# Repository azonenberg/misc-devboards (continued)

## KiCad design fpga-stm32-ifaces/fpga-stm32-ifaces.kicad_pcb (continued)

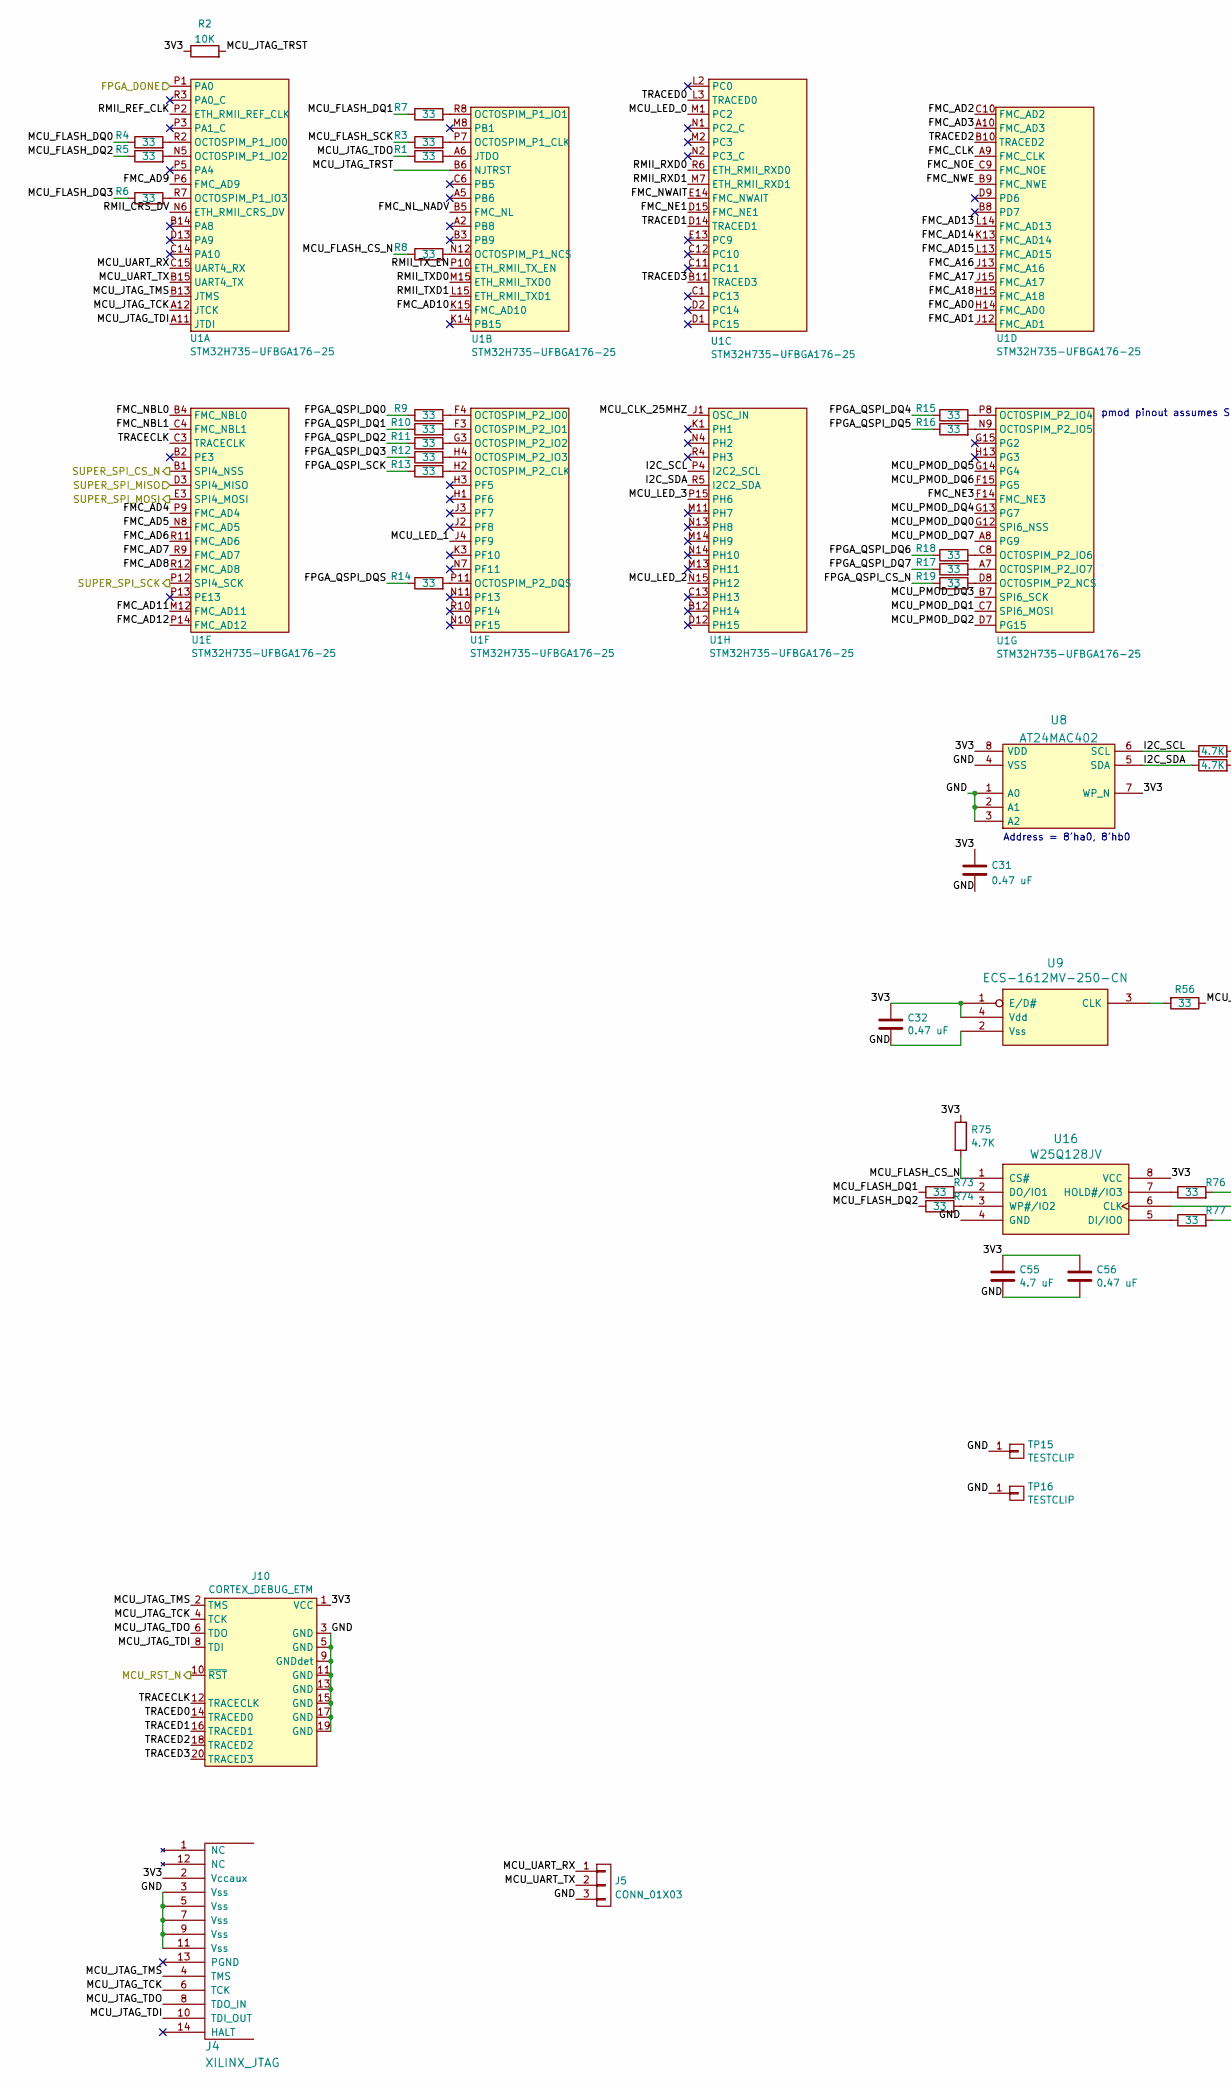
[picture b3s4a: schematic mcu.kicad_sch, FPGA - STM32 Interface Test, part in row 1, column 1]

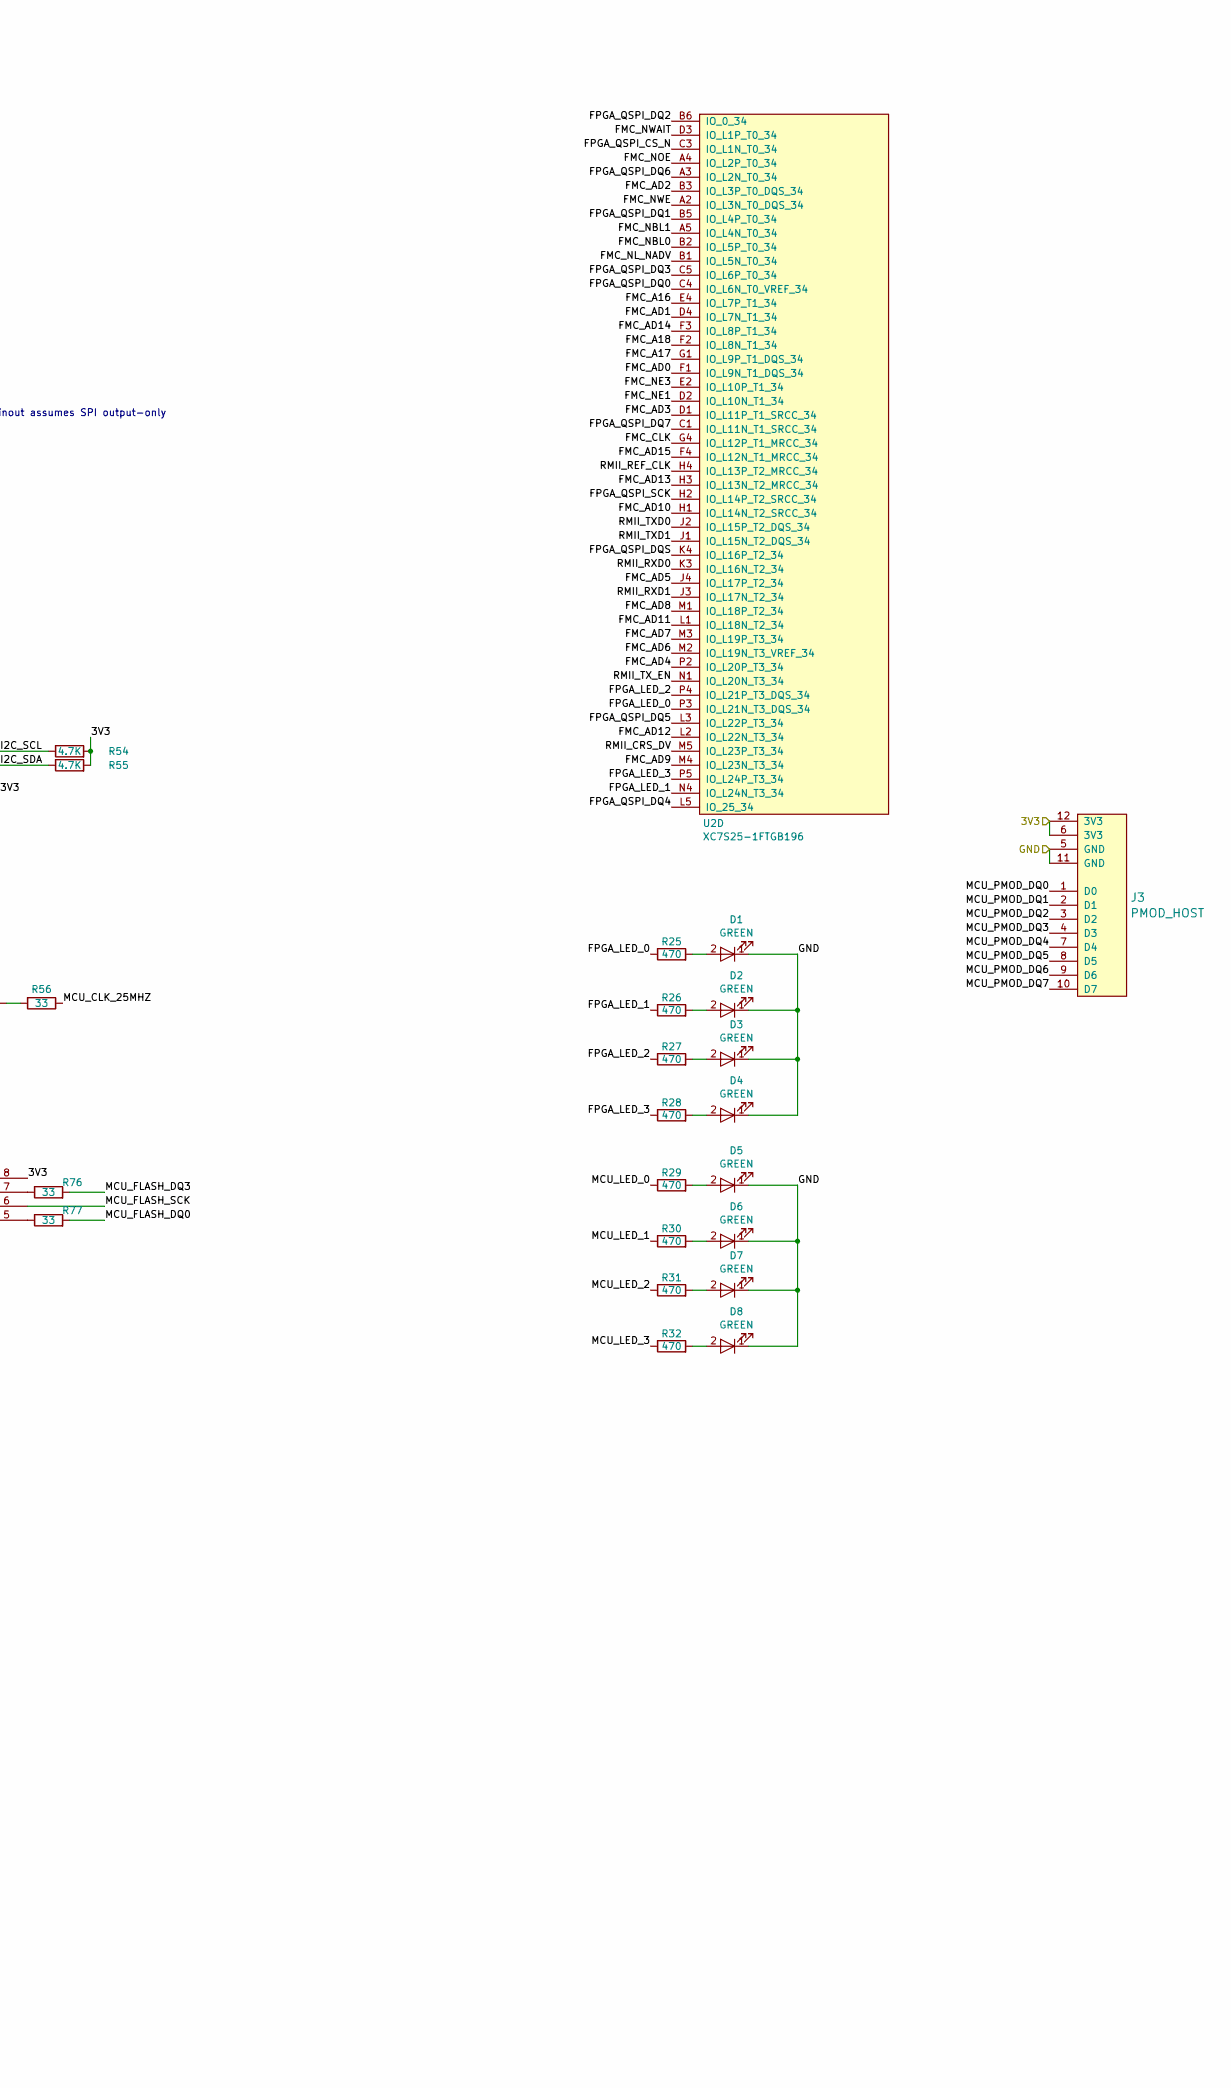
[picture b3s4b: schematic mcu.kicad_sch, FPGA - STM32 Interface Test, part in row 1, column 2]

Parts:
C31, C32, C56: 0.47 uF; EIA_0402_CAP_NOSILK
C55: 4.7 uF; EIA_0603_CAP_NOSILK
D1, D2, D3, D4, D5, D6, D7, D8: GREEN; EIA_0603_LED
J3: PMOD_HOST; CONN_HEADER_2.54MM_2x6_RA_PMOD_HOST
J4: XILINX_JTAG; XILINX_JTAG_PTH_MOLEX_0878311420
J5: CONN_01X03; CONN_HEADER_2.54MM_1x3
J10: CORTEX_DEBUG_ETM; CONN_HEADER_1.27MM_2x10_SMT_SAMTEC_FTSH-110-01-L-DV-K
R1, R3, R4, R5, R6, R7, R8, R9, R10, R11, R12, R13, R14, R15, R16, R17, R18, R19, R56, R73, R74, R76, R77: 33; EIA_0402_RES_NOSILK
R2: 10K; EIA_0402_RES_NOSILK
R25, R26, R27, R28, R29, R30, R31, R32: 470; EIA_0402_RES_NOSILK
R54, R55, R75: 4.7K; EIA_0402_RES_NOSILK
TP15, TP16: TESTCLIP; TESTPOINT_SMT_KEYSTONE_5016
U1: STM32H735-UFBGA176-25; BGA_201_10x10_DEPOP_0.65MM_OSHPARK
U2: XC7S25-1FTGB196; BGA_196_15x15_FULLARRAY_1MM_FTGB196
U8: AT24MAC402; DFN_8_0.5MM_2x3MM_TALL
U9: ECS-1612MV-250-CN; OSCILLATOR_1.6x1.2
U16: W25Q128JV; DFN_8_1.27MM_6x5MM

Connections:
/3V3: C31.1, C32.1, C55.1, C56.1, J3.6 (3V3), J3.12 (3V3), J4.2 (Vccaux), J10.1 (VCC), R2.1, R54.2, R55.2, R75.1, U8.7 (WP_N), U8.8 (VDD), U9.1 (E/D#), U9.4 (Vdd), U16.8 (VCC); also elsewhere on the board
/FPGA_DONE: U1.P1 (PA0); also elsewhere on the board
/GND: C31.2, C32.2, C55.2, C56.2, D1.1 (K), D2.1 (K), D3.1 (K), D4.1 (K), D5.1 (K), D6.1 (K), D7.1 (K), D8.1 (K), J3.5 (GND), J3.11 (GND), J4.3 (Vss), J4.5 (Vss), J4.7 (Vss), J4.9 (Vss), J4.11 (Vss), J5.3, J10.3 (GND), J10.5 (GND), J10.9 (GNDdet), J10.11 (GND), J10.13 (GND), J10.15 (GND), J10.17 (GND), J10.19 (GND), TP15.1, TP16.1, U8.1 (A0), U8.2 (A1), U8.3 (A2), U8.4 (VSS), U9.2 (Vss), U16.4 (GND); also elsewhere on the board
/MCU/FMC_A16: U1.J13 (FMC_A16), U2.E4 (IO_L7P_T1_34)
/MCU/FMC_A17: U1.J15 (FMC_A17), U2.G1 (IO_L9P_T1_DQS_34)
/MCU/FMC_A18: U1.H15 (FMC_A18), U2.F2 (IO_L8N_T1_34)
/MCU/FMC_AD0: U1.H14 (FMC_AD0), U2.F1 (IO_L9N_T1_DQS_34)
/MCU/FMC_AD1: U1.J12 (FMC_AD1), U2.D4 (IO_L7N_T1_34)
/MCU/FMC_AD2: U1.C10 (FMC_AD2), U2.B3 (IO_L3P_T0_DQS_34)
/MCU/FMC_AD3: U1.A10 (FMC_AD3), U2.D1 (IO_L11P_T1_SRCC_34)
/MCU/FMC_AD4: U1.P9 (FMC_AD4), U2.P2 (IO_L20P_T3_34)
/MCU/FMC_AD5: U1.N8 (FMC_AD5), U2.J4 (IO_L17P_T2_34)
/MCU/FMC_AD6: U1.R11 (FMC_AD6), U2.M2 (IO_L19N_T3_VREF_34)
/MCU/FMC_AD7: U1.R9 (FMC_AD7), U2.M3 (IO_L19P_T3_34)
/MCU/FMC_AD8: U1.R12 (FMC_AD8), U2.M1 (IO_L18P_T2_34)
/MCU/FMC_AD9: U1.P6 (FMC_AD9), U2.M4 (IO_L23N_T3_34)
/MCU/FMC_AD10: U1.K15 (FMC_AD10), U2.H1 (IO_L14N_T2_SRCC_34)
/MCU/FMC_AD11: U1.M12 (FMC_AD11), U2.L1 (IO_L18N_T2_34)
/MCU/FMC_AD12: U1.P14 (FMC_AD12), U2.L2 (IO_L22N_T3_34)
/MCU/FMC_AD13: U1.L14 (FMC_AD13), U2.H3 (IO_L13N_T2_MRCC_34)
/MCU/FMC_AD14: U1.K13 (FMC_AD14), U2.F3 (IO_L8P_T1_34)
/MCU/FMC_AD15: U1.L13 (FMC_AD15), U2.F4 (IO_L12N_T1_MRCC_34)
/MCU/FMC_CLK: U1.A9 (FMC_CLK), U2.G4 (IO_L12P_T1_MRCC_34)
/MCU/FMC_NBL0: U1.B4 (FMC_NBL0), U2.B2 (IO_L5P_T0_34)
/MCU/FMC_NBL1: U1.C4 (FMC_NBL1), U2.A5 (IO_L4N_T0_34)
/MCU/FMC_NE1: U1.D15 (FMC_NE1), U2.D2 (IO_L10N_T1_34)
/MCU/FMC_NE3: U1.F14 (FMC_NE3), U2.E2 (IO_L10P_T1_34)
/MCU/FMC_NL_NADV: U1.B5 (FMC_NL), U2.B1 (IO_L5N_T0_34)
/MCU/FMC_NOE: U1.C9 (FMC_NOE), U2.A4 (IO_L2P_T0_34)
/MCU/FMC_NWAIT: U1.E14 (FMC_NWAIT), U2.D3 (IO_L1P_T0_34)
/MCU/FMC_NWE: U1.B9 (FMC_NWE), U2.A2 (IO_L3N_T0_DQS_34)
/MCU/FPGA_LED_0: R25.1, U2.P3 (IO_L21N_T3_DQS_34)
/MCU/FPGA_LED_1: R26.1, U2.N4 (IO_L24N_T3_34)
/MCU/FPGA_LED_2: R27.1, U2.P4 (IO_L21P_T3_DQS_34)
/MCU/FPGA_LED_3: R28.1, U2.P5 (IO_L24P_T3_34)
/MCU/FPGA_QSPI_CS_N: R19.1, U2.C3 (IO_L1N_T0_34)
/MCU/FPGA_QSPI_DQ0: R9.1, U2.C4 (IO_L6N_T0_VREF_34)
/MCU/FPGA_QSPI_DQ1: R10.1, U2.B5 (IO_L4P_T0_34)
/MCU/FPGA_QSPI_DQ2: R11.1, U2.B6 (IO_0_34)
/MCU/FPGA_QSPI_DQ3: R12.1, U2.C5 (IO_L6P_T0_34)
/MCU/FPGA_QSPI_DQ4: R15.1, U2.L5 (IO_25_34)
/MCU/FPGA_QSPI_DQ5: R16.1, U2.L3 (IO_L22P_T3_34)
/MCU/FPGA_QSPI_DQ6: R18.1, U2.A3 (IO_L2N_T0_34)
/MCU/FPGA_QSPI_DQ7: R17.1, U2.C1 (IO_L11N_T1_SRCC_34)
/MCU/FPGA_QSPI_DQS: R14.1, U2.K4 (IO_L16P_T2_34)
/MCU/FPGA_QSPI_SCK: R13.1, U2.H2 (IO_L14P_T2_SRCC_34)
/MCU/I2C_SCL: R54.1, U1.P4 (I2C2_SCL), U8.6 (SCL)
/MCU/I2C_SDA: R55.1, U1.R5 (I2C2_SDA), U8.5 (SDA)
/MCU/MCU_CLK_25MHZ: R56.1, U1.J1 (OSC_IN)
/MCU/MCU_FLASH_CS_N: R8.1, R75.2, U16.1 (CS#)
/MCU/MCU_FLASH_DQ0: R4.1, R77.2
/MCU/MCU_FLASH_DQ1: R7.1, R73.1
/MCU/MCU_FLASH_DQ2: R5.1, R74.1
/MCU/MCU_FLASH_DQ3: R6.1, R76.2
/MCU/MCU_FLASH_SCK: R3.1, U16.6 (CLK)
/MCU/MCU_JTAG_TCK: J4.6 (TCK), J10.4 (TCK), U1.A12 (JTCK)
/MCU/MCU_JTAG_TDI: J4.10 (TDI_OUT), J10.8 (TDI), U1.A11 (JTDI)
/MCU/MCU_JTAG_TDO: J4.8 (TDO_IN), J10.6 (TDO), R1.1
/MCU/MCU_JTAG_TMS: J4.4 (TMS), J10.2 (TMS), U1.B13 (JTMS)
/MCU/MCU_JTAG_TRST: R2.2, U1.B6 (NJTRST)
/MCU/MCU_LED_0: R29.1, U1.M1 (PC2)
/MCU/MCU_LED_1: R30.1, U1.J4 (PF9)
/MCU/MCU_LED_2: R31.1, U1.N15 (PH12)
/MCU/MCU_LED_3: R32.1, U1.P15 (PH6)
/MCU/MCU_PMOD_DQ0: J3.1 (D0), U1.G12 (SPI6_NSS)
/MCU/MCU_PMOD_DQ1: J3.2 (D1), U1.C7 (SPI6_MOSI)
/MCU/MCU_PMOD_DQ2: J3.3 (D2), U1.D7 (PG15)
/MCU/MCU_PMOD_DQ3: J3.4 (D3), U1.B7 (SPI6_SCK)
/MCU/MCU_PMOD_DQ4: J3.7 (D4), U1.G13 (PG7)
/MCU/MCU_PMOD_DQ5: J3.8 (D5), U1.G14 (PG4)
/MCU/MCU_PMOD_DQ6: J3.9 (D6), U1.F15 (PG5)
/MCU/MCU_PMOD_DQ7: J3.10 (D7), U1.A8 (PG9)
/MCU/MCU_UART_RX: J5.1, U1.C15 (UART4_RX)
/MCU/MCU_UART_TX: J5.2, U1.B15 (UART4_TX)
/MCU/RMII_CRS_DV: U1.N6 (ETH_RMII_CRS_DV), U2.M5 (IO_L23P_T3_34)
/MCU/RMII_REF_CLK: U1.P2 (ETH_RMII_REF_CLK), U2.H4 (IO_L13P_T2_MRCC_34)
/MCU/RMII_RXD0: U1.R6 (ETH_RMII_RXD0), U2.K3 (IO_L16N_T2_34)
/MCU/RMII_RXD1: U1.M7 (ETH_RMII_RXD1), U2.J3 (IO_L17N_T2_34)
/MCU/RMII_TXD0: U1.M15 (ETH_RMII_TXD0), U2.J2 (IO_L15P_T2_DQS_34)
/MCU/RMII_TXD1: U1.L15 (ETH_RMII_TXD1), U2.J1 (IO_L15N_T2_DQS_34)
/MCU/RMII_TX_EN: U1.P10 (ETH_RMII_TX_EN), U2.N1 (IO_L20N_T3_34)
/MCU/SUPER_SPI_CS_N: U1.B1 (SPI4_NSS); also elsewhere on the board
/MCU/SUPER_SPI_MISO: U1.D3 (SPI4_MISO); also elsewhere on the board
/MCU/SUPER_SPI_MOSI: U1.E3 (SPI4_MOSI); also elsewhere on the board
/MCU/SUPER_SPI_SCK: U1.P12 (SPI4_SCK); also elsewhere on the board
/MCU/TRACECLK: J10.12 (TRACECLK), U1.C3 (TRACECLK)
/MCU/TRACED0: J10.14 (TRACED0), U1.L3 (TRACED0)
/MCU/TRACED1: J10.16 (TRACED1), U1.D14 (TRACED1)
/MCU/TRACED2: J10.18 (TRACED2), U1.B10 (TRACED2)
/MCU/TRACED3: J10.20 (TRACED3), U1.B11 (TRACED3)
/MCU_RST_N: J10.10 (~RST); also elsewhere on the board
unnamed: D1.2 (A), R25.2
unnamed: D2.2 (A), R26.2
unnamed: D3.2 (A), R27.2
unnamed: D4.2 (A), R28.2
unnamed: D5.2 (A), R29.2
unnamed: D6.2 (A), R30.2
unnamed: D7.2 (A), R31.2
unnamed: D8.2 (A), R32.2
unnamed: R4.2, U1.R2 (OCTOSPIM_P1_IO0)
unnamed: R5.2, U1.N5 (OCTOSPIM_P1_IO2)
unnamed: R6.2, U1.R7 (OCTOSPIM_P1_IO3)
unnamed: R7.2, U1.R8 (OCTOSPIM_P1_IO1)
unnamed: R3.2, U1.P7 (OCTOSPIM_P1_CLK)
unnamed: R1.2, U1.A6 (JTDO)
unnamed: R8.2, U1.N12 (OCTOSPIM_P1_NCS)
unnamed: R9.2, U1.F4 (OCTOSPIM_P2_IO0)
unnamed: R10.2, U1.F3 (OCTOSPIM_P2_IO1)
unnamed: R11.2, U1.G3 (OCTOSPIM_P2_IO2)
unnamed: R12.2, U1.H4 (OCTOSPIM_P2_IO3)
unnamed: R13.2, U1.H2 (OCTOSPIM_P2_CLK)
unnamed: R14.2, U1.P11 (OCTOSPIM_P2_DQS)
unnamed: R15.2, U1.P8 (OCTOSPIM_P2_IO4)
unnamed: R16.2, U1.N9 (OCTOSPIM_P2_IO5)
unnamed: R18.2, U1.C8 (OCTOSPIM_P2_IO6)
unnamed: R17.2, U1.A7 (OCTOSPIM_P2_IO7)
unnamed: R19.2, U1.D8 (OCTOSPIM_P2_NCS)
unnamed: R56.2, U9.3 (CLK)
unnamed: R77.1, U16.5 (DI/IO0)
unnamed: R73.2, U16.2 (DO/IO1)
unnamed: R76.1, U16.7 (HOLD#/IO3)
unnamed: R74.2, U16.3 (WP#/IO2)

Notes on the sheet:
pmod pinout assumes SPI output-only
Address = 8'ha0, 8'hb0

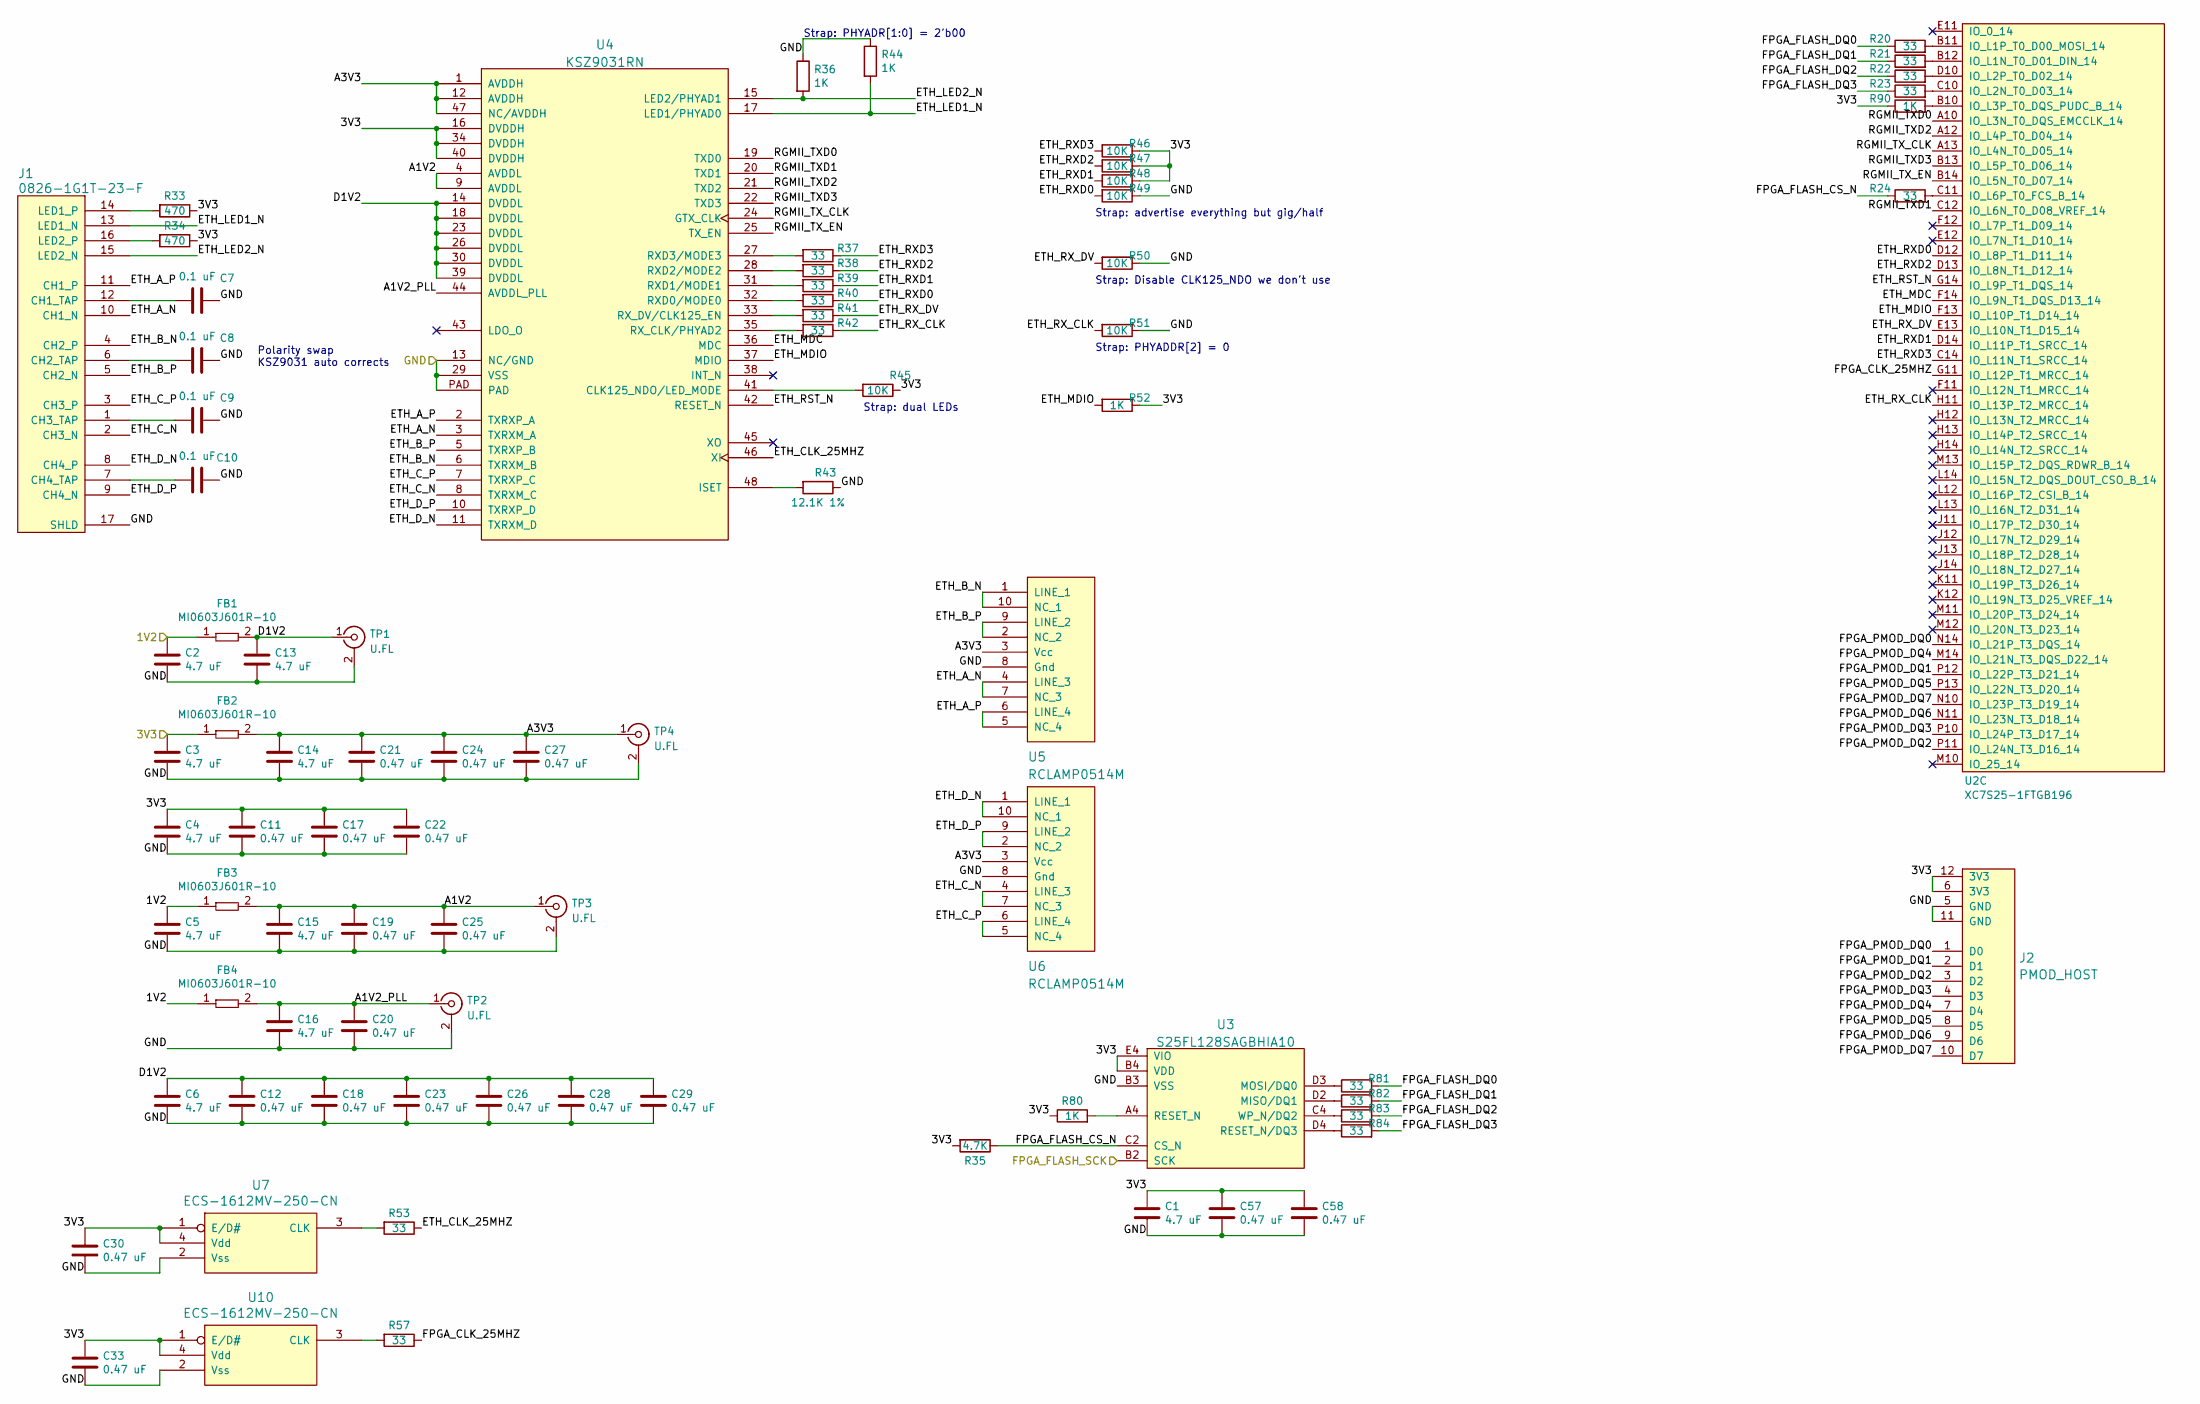
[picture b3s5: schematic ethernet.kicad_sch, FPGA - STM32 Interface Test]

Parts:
C1, C2, C3, C4, C5, C6, C13, C14, C15, C16: 4.7 uF; EIA_0603_CAP_NOSILK
C7, C8, C9, C10: 0.1 uF; EIA_0402_CAP_NOSILK
C11, C12, C17, C18, C19, C20, C21, C22, C23, C24, C25, C26, C27, C28, C29, C30, C33, C57, C58: 0.47 uF; EIA_0402_CAP_NOSILK
FB1, FB2, FB3, FB4: MI0603J601R-10; EIA_0603_INDUCTOR_NOSILK
J1: 0826-1G1T-23-F; CONN_BELFUSE_0826_1G1T_23_F
J2: PMOD_HOST; CONN_HEADER_2.54MM_2x6_RA_PMOD_HOST
R20, R21, R22, R23, R24, R37, R38, R39, R40, R41, R42, R53, R57, R81, R82, R83, R84: 33; EIA_0402_RES_NOSILK
R33, R34: 470; EIA_0402_RES_NOSILK
R35: 4.7K; EIA_0402_RES_NOSILK
R36, R44, R52, R80, R90: 1K; EIA_0402_RES_NOSILK
R43: 12.1K 1%; EIA_0402_RES_NOSILK
R45, R46, R47, R48, R49, R50, R51: 10K; EIA_0402_RES_NOSILK
TP1, TP2, TP3, TP4: U.FL; CONN_U.FL_TE_1909763-1
U2: XC7S25-1FTGB196; BGA_196_15x15_FULLARRAY_1MM_FTGB196
U3: S25FL128SAGBHIA10; BGA_24_6x8_DEPOP1_1MM
U4: KSZ9031RN; QFN_48_0.5MM_7x7MM
U5, U6: RCLAMP0514M; SOP_10_0.5MM_3MM
U7, U10: ECS-1612MV-250-CN; OSCILLATOR_1.6x1.2

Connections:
/3V3: C1.1, C3.1, C4.1, C11.1, C17.1, C22.1, C30.1, C33.1, C57.1, C58.1, FB2.1, J2.6 (3V3), J2.12 (3V3), R33.1, R34.1, R35.2, R45.1, R46.1, R47.1, R48.1, R52.1, R80.1, R90.1, U3.B4 (VDD), U3.E4 (VIO), U4.16 (DVDDH), U4.34 (DVDDH), U4.40 (DVDDH), U7.1 (E/D#), U7.4 (Vdd), U10.1 (E/D#), U10.4 (Vdd); also elsewhere on the board
/Ethernet/1V2: C2.1, C5.1, FB1.1, FB3.1, FB4.1; also elsewhere on the board
/Ethernet/A1V2: C15.1, C19.1, C25.1, FB3.2, TP3.1 (In), U4.4 (AVDDL), U4.9 (AVDDL)
/Ethernet/A1V2_PLL: C16.1, C20.1, FB4.2, TP2.1 (In), U4.44 (AVDDL_PLL)
/Ethernet/A3V3: C14.1, C21.1, C24.1, C27.1, FB2.2, TP4.1 (In), U4.1 (AVDDH), U4.12 (AVDDH), U4.47 (NC/AVDDH), U5.3 (Vcc), U6.3 (Vcc)
/Ethernet/D1V2: C6.1, C12.1, C13.1, C18.1, C23.1, C26.1, C28.1, C29.1, FB1.2, TP1.1 (In), U4.14 (DVDDL), U4.18 (DVDDL), U4.23 (DVDDL), U4.26 (DVDDL), U4.30 (DVDDL), U4.39 (DVDDL)
/Ethernet/ETH_A_N: J1.10 (CH1_N), U4.3 (TXRXM_A), U5.4 (LINE_3), U5.7 (NC_3)
/Ethernet/ETH_A_P: J1.11 (CH1_P), U4.2 (TXRXP_A), U5.5 (NC_4), U5.6 (LINE_4)
/Ethernet/ETH_B_N: J1.4 (CH2_P), U4.6 (TXRXM_B), U5.1 (LINE_1), U5.10 (NC_1)
/Ethernet/ETH_B_P: J1.5 (CH2_N), U4.5 (TXRXP_B), U5.2 (NC_2), U5.9 (LINE_2)
/Ethernet/ETH_CLK_25MHZ: R53.1, U4.46 (XI)
/Ethernet/ETH_C_N: J1.2 (CH3_N), U4.8 (TXRXM_C), U6.4 (LINE_3), U6.7 (NC_3)
/Ethernet/ETH_C_P: J1.3 (CH3_P), U4.7 (TXRXP_C), U6.5 (NC_4), U6.6 (LINE_4)
/Ethernet/ETH_D_N: J1.8 (CH4_P), U4.11 (TXRXM_D), U6.1 (LINE_1), U6.10 (NC_1)
/Ethernet/ETH_D_P: J1.9 (CH4_N), U4.10 (TXRXP_D), U6.2 (NC_2), U6.9 (LINE_2)
/Ethernet/ETH_LED1_N: J1.13 (LED1_N), R44.2, U4.17 (LED1/PHYAD0)
/Ethernet/ETH_LED2_N: J1.15 (LED2_N), R36.2, U4.15 (LED2/PHYAD1)
/Ethernet/ETH_MDC: U2.F14 (IO_L9N_T1_DQS_D13_14), U4.36 (MDC)
/Ethernet/ETH_MDIO: R52.2, U2.F13 (IO_L10P_T1_D14_14), U4.37 (MDIO)
/Ethernet/ETH_RST_N: U2.G14 (IO_L9P_T1_DQS_14), U4.42 (RESET_N)
/Ethernet/ETH_RXD0: R40.1, R49.2, U2.D12 (IO_L8P_T1_D11_14)
/Ethernet/ETH_RXD1: R39.1, R48.2, U2.D14 (IO_L11P_T1_SRCC_14)
/Ethernet/ETH_RXD2: R38.1, R47.2, U2.D13 (IO_L8N_T1_D12_14)
/Ethernet/ETH_RXD3: R37.1, R46.2, U2.C14 (IO_L11N_T1_SRCC_14)
/Ethernet/ETH_RX_CLK: R42.1, R51.2, U2.H11 (IO_L13P_T2_MRCC_14)
/Ethernet/ETH_RX_DV: R41.1, R50.2, U2.E13 (IO_L10N_T1_D15_14)
/Ethernet/FPGA_CLK_25MHZ: R57.1, U2.G11 (IO_L12P_T1_MRCC_14)
/Ethernet/FPGA_FLASH_CS_N: R24.1, R35.1, U3.C2 (CS_N)
/Ethernet/FPGA_FLASH_DQ0: R20.1, R81.2
/Ethernet/FPGA_FLASH_DQ1: R21.1, R82.2
/Ethernet/FPGA_FLASH_DQ2: R22.1, R83.2
/Ethernet/FPGA_FLASH_DQ3: R23.1, R84.2
/Ethernet/FPGA_PMOD_DQ0: J2.1 (D0), U2.N14 (IO_L21P_T3_DQS_14)
/Ethernet/FPGA_PMOD_DQ1: J2.2 (D1), U2.P12 (IO_L22P_T3_D21_14)
/Ethernet/FPGA_PMOD_DQ2: J2.3 (D2), U2.P11 (IO_L24N_T3_D16_14)
/Ethernet/FPGA_PMOD_DQ3: J2.4 (D3), U2.P10 (IO_L24P_T3_D17_14)
/Ethernet/FPGA_PMOD_DQ4: J2.7 (D4), U2.M14 (IO_L21N_T3_DQS_D22_14)
/Ethernet/FPGA_PMOD_DQ5: J2.8 (D5), U2.P13 (IO_L22N_T3_D20_14)
/Ethernet/FPGA_PMOD_DQ6: J2.9 (D6), U2.N11 (IO_L23N_T3_D18_14)
/Ethernet/FPGA_PMOD_DQ7: J2.10 (D7), U2.N10 (IO_L23P_T3_D19_14)
/Ethernet/RGMII_TXD0: U2.A10 (IO_L3N_T0_DQS_EMCCLK_14), U4.19 (TXD0)
/Ethernet/RGMII_TXD1: U2.C12 (IO_L6N_T0_D08_VREF_14), U4.20 (TXD1)
/Ethernet/RGMII_TXD2: U2.A12 (IO_L4P_T0_D04_14), U4.21 (TXD2)
/Ethernet/RGMII_TXD3: U2.B13 (IO_L5P_T0_D06_14), U4.22 (TXD3)
/Ethernet/RGMII_TX_CLK: U2.A13 (IO_L4N_T0_D05_14), U4.24 (GTX_CLK)
/Ethernet/RGMII_TX_EN: U2.B14 (IO_L5N_T0_D07_14), U4.25 (TX_EN)
/FPGA_FLASH_SCK: U3.B2 (SCK); also elsewhere on the board
/GND: C1.2, C2.2, C3.2, C4.2, C5.2, C6.2, C7.1, C8.1, C9.1, C10.1, C11.2, C12.2, C13.2, C14.2, C15.2, C16.2, C17.2, C18.2, C19.2, C20.2, C21.2, C22.2, C23.2, C24.2, C25.2, C26.2, C27.2, C28.2, C29.2, C30.2, C33.2, C57.2, C58.2, J1.17 (SHLD), J2.5 (GND), J2.11 (GND), R36.1, R43.1, R44.1, R49.1, R50.1, R51.1, TP1.2 (Ext), TP2.2 (Ext), TP3.2 (Ext), TP4.2 (Ext), U3.B3 (VSS), U4.13 (NC/GND), U4.29 (VSS), U4.PAD, U5.8 (Gnd), U6.8 (Gnd), U7.2 (Vss), U10.2 (Vss); also elsewhere on the board
unnamed: C7.2, J1.12 (CH1_TAP)
unnamed: C8.2, J1.6 (CH2_TAP)
unnamed: C9.2, J1.1 (CH3_TAP)
unnamed: C10.2, J1.7 (CH4_TAP)
unnamed: J1.14 (LED1_P), R33.2
unnamed: J1.16 (LED2_P), R34.2
unnamed: R21.2, U2.B12 (IO_L1N_T0_D01_DIN_14)
unnamed: R20.2, U2.B11 (IO_L1P_T0_D00_MOSI_14)
unnamed: R23.2, U2.C10 (IO_L2N_T0_D03_14)
unnamed: R22.2, U2.D10 (IO_L2P_T0_D02_14)
unnamed: R90.2, U2.B10 (IO_L3P_T0_DQS_PUDC_B_14)
unnamed: R24.2, U2.C11 (IO_L6P_T0_FCS_B_14)
unnamed: R82.1, U3.D2 (MISO/DQ1)
unnamed: R81.1, U3.D3 (MOSI/DQ0)
unnamed: R80.2, U3.A4 (RESET_N)
unnamed: R84.1, U3.D4 (RESET_N/DQ3)
unnamed: R83.1, U3.C4 (WP_N/DQ2)
unnamed: R45.2, U4.41 (CLK125_NDO/LED_MODE)
unnamed: R43.2, U4.48 (ISET)
unnamed: R40.2, U4.32 (RXD0/MODE0)
unnamed: R39.2, U4.31 (RXD1/MODE1)
unnamed: R38.2, U4.28 (RXD2/MODE2)
unnamed: R37.2, U4.27 (RXD3/MODE3)
unnamed: R42.2, U4.35 (RX_CLK/PHYAD2)
unnamed: R41.2, U4.33 (RX_DV/CLK125_EN)
unnamed: R53.2, U7.3 (CLK)
unnamed: R57.2, U10.3 (CLK)

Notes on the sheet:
Strap: dual LEDs
Strap: Disable CLK125_NDO we don't use
Strap: PHYADR[1:0] = 2'b00
Polarity swap KSZ9031 auto corrects
Strap: advertise everything but gig/half
Strap: PHYADDR[2] = 0

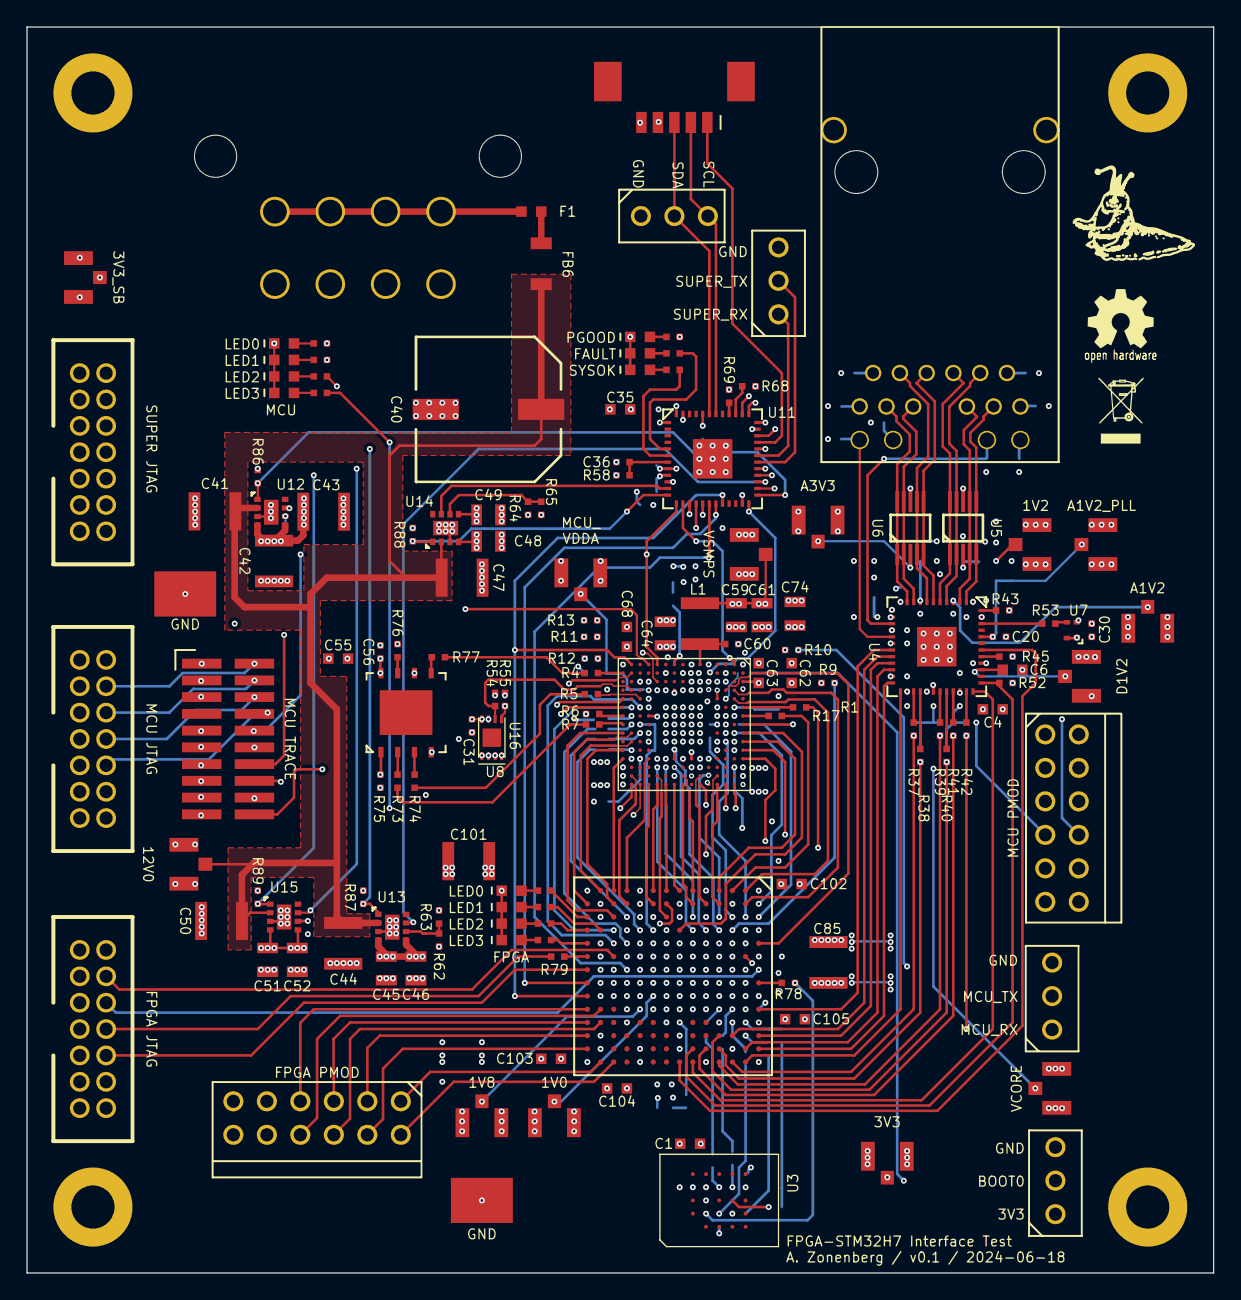
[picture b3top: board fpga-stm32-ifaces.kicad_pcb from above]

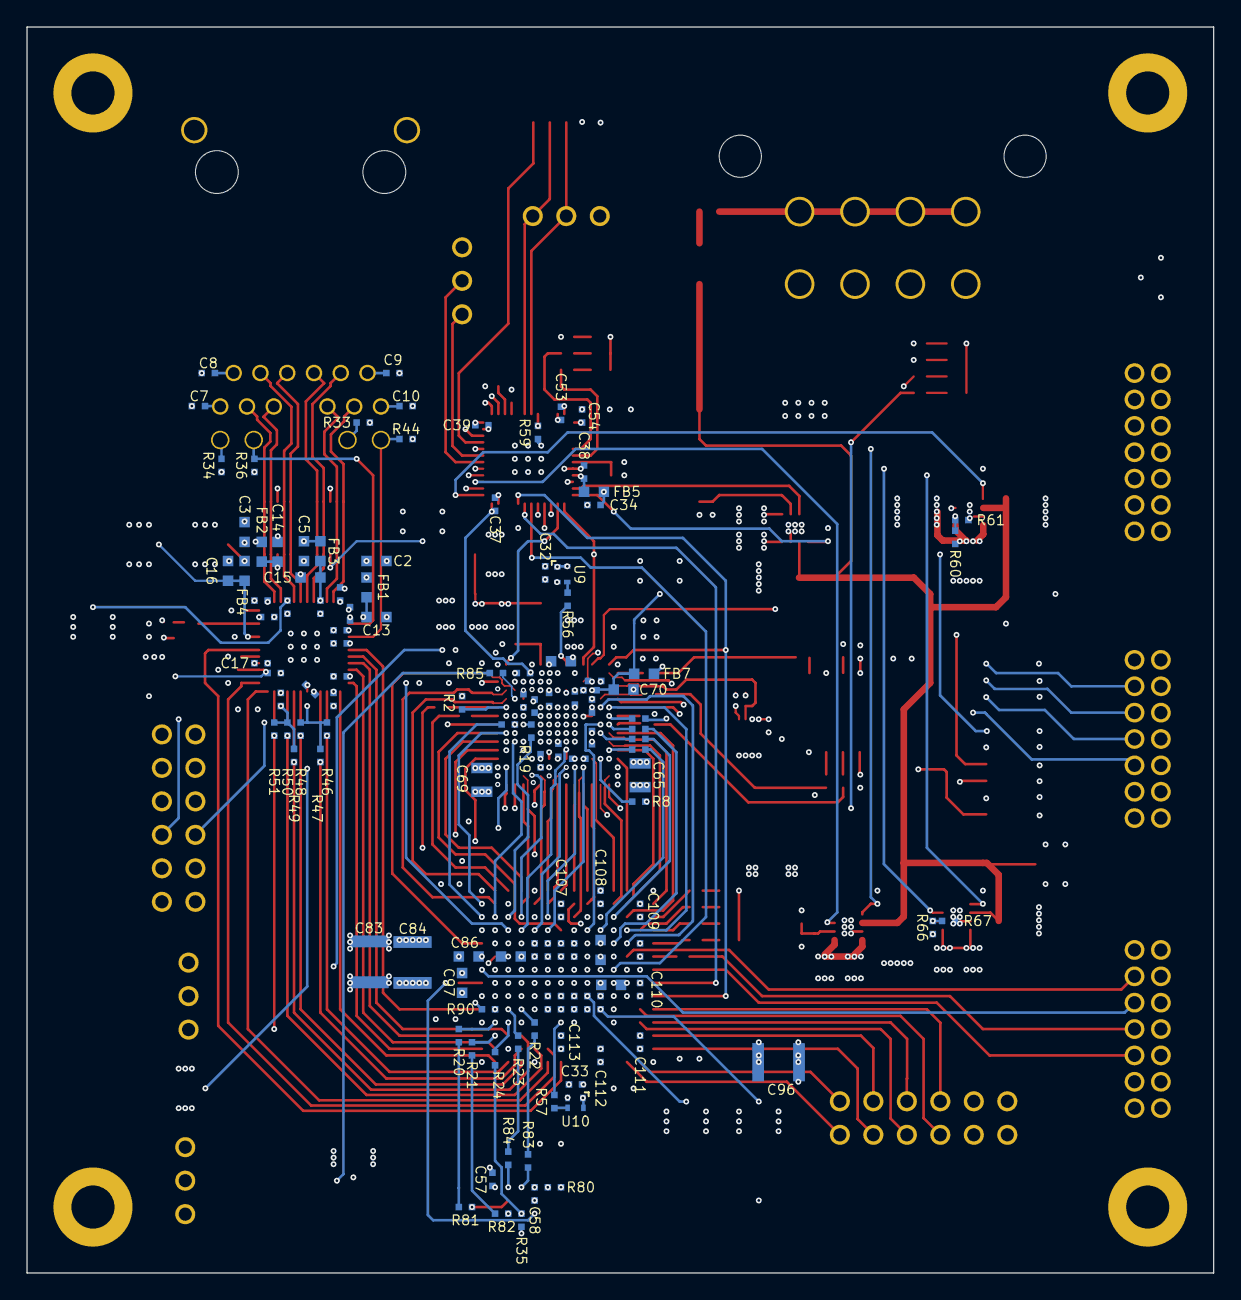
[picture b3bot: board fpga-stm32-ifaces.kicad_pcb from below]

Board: 6 copper layers, 90.0 x 94.5 mm, 274 parts (122 on the bottom side), 247 nets.

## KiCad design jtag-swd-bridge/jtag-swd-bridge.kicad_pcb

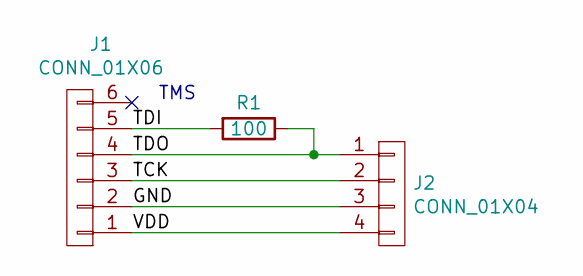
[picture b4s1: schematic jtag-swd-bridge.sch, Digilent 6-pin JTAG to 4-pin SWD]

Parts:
J1: CONN_01X06; CONN_HEADER_2.54MM_1x6
J2: CONN_01X04; CONN_HEADER_2.54MM_1x4
R1: 100; EIA_0402_RES_NOSILK

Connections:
/GND: J1.2, J2.3
/TCK: J1.3, J2.2
/TDI: J1.5, R1.2
/TDO: J1.4, J2.1, R1.1
/VDD: J1.1, J2.4

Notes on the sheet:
TMS

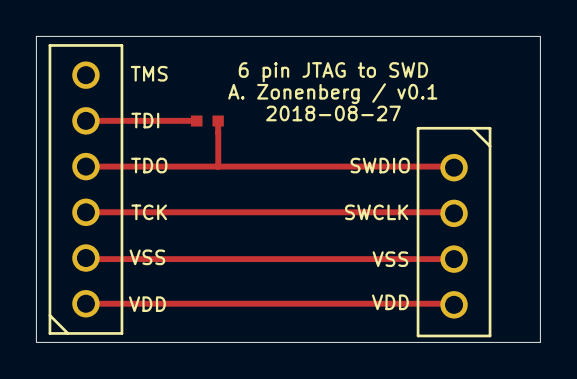
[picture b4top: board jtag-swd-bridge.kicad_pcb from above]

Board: 4 copper layers, 28.0 x 17.0 mm, 3 parts (0 on the bottom side), 5 nets.
